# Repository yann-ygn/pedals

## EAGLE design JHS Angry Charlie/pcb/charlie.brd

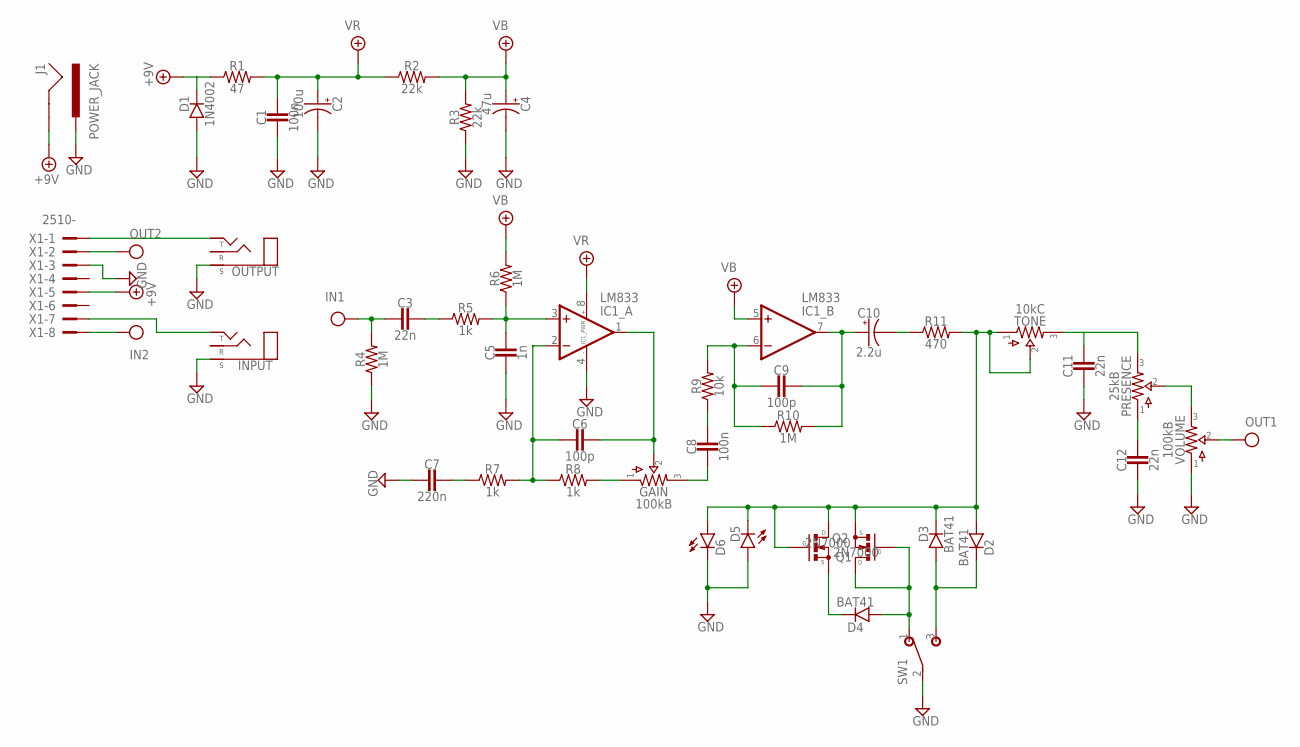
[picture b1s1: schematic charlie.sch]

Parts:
C1: 100n; 050X030_025_2
C2: 100u; 050_020
C3, C11, C12: 22n; BOX_SMALL
C4: 47u; 050_020
C5: 1n; BOX_SMALL
C6, C9: 100p; 050X030_025_2
C7: 220n; BOX_SMALL
C8: 100n; BOX_SMALL
C10: 2.2u; 050_020
D1: 1N4002; DO41-2
D2, D3, D4: BAT41; DO35-2
D5, D6: LED; 3MM_D
GAIN: 100kB; 16MM
IC1: LM833; DIL08
INPUT: STEREONMJ; NMJ6HCD2
J1: POWER_JACK; POWER_JACK_PTH
OUTPUT: STEREONMJ; NMJ6HCD2
PRESENCE: 25kB; 16MM
Q1, Q2: 2N7000; TO92-
R1: 47; R0207/3
R2, R3: 22k; R0207/3
R4, R6, R10: 1M; R0207/3
R5, R7, R8: 1k; R0207/3
R9: 10k; R0207/3
R11: 470; R0207/3
SW1: SPDT; M9040P
TONE: 10kC; 16MM
VOLUME: 100kB; 16MM
X1: 2510-; PAK100/2500-10

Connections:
+9V: D1.C, J1.GND, R1.1, X1.5
GND: C1.2, C2.-, C4.-, C5.2, C7.2, C11.2, C12.2, D1.A, D5.ANODE (A), D6.P$1 (C), IC1.4 (V-), INPUT.S, J1.PWR, OUTPUT.S, R3.1, R4.1, SW1.2, VOLUME.1, X1.3
IN: C3.2, R4.2, X1.8
unnamed: C3.1, R5.1
unnamed: INPUT.T, X1.7
unnamed: C5.1, IC1.3 (+IN), R5.2, R6.1
unnamed: OUTPUT.T, X1.1
unnamed: C6.2, IC1.2 (-IN), R7.2, R8.1
unnamed: C7.1, R7.1
unnamed: C6.1, GAIN.2, IC1.1 (OUT)
unnamed: C11.1, PRESENCE.3, TONE.3
unnamed: GAIN.1, R8.2
unnamed: C8.2, GAIN.3
unnamed: C8.1, R9.1
unnamed: C9.2, IC1.6 (-IN), R9.2, R10.1
unnamed: C9.1, C10.+, IC1.7 (OUT), R10.2
unnamed: C10.-, R11.1
unnamed: D4.A, Q1.1 (D), Q1.2 (G), SW1.1 (O)
unnamed: D4.C, Q2.3 (S)
unnamed: D2.A, D3.C, D5.P$1 (C), D6.ANODE (A), Q1.3 (S), Q2.1 (D), Q2.2 (G), R11.2, TONE.1, TONE.2
unnamed: D2.C, D3.A, SW1.3 (S)
unnamed: C12.1, PRESENCE.1
unnamed: PRESENCE.2, VOLUME.3
OUT: VOLUME.2, X1.2
VB: C4.+, IC1.5 (+IN), R2.2, R3.2, R6.2
VR: C1.1, C2.+, IC1.8 (V+), R1.2, R2.1

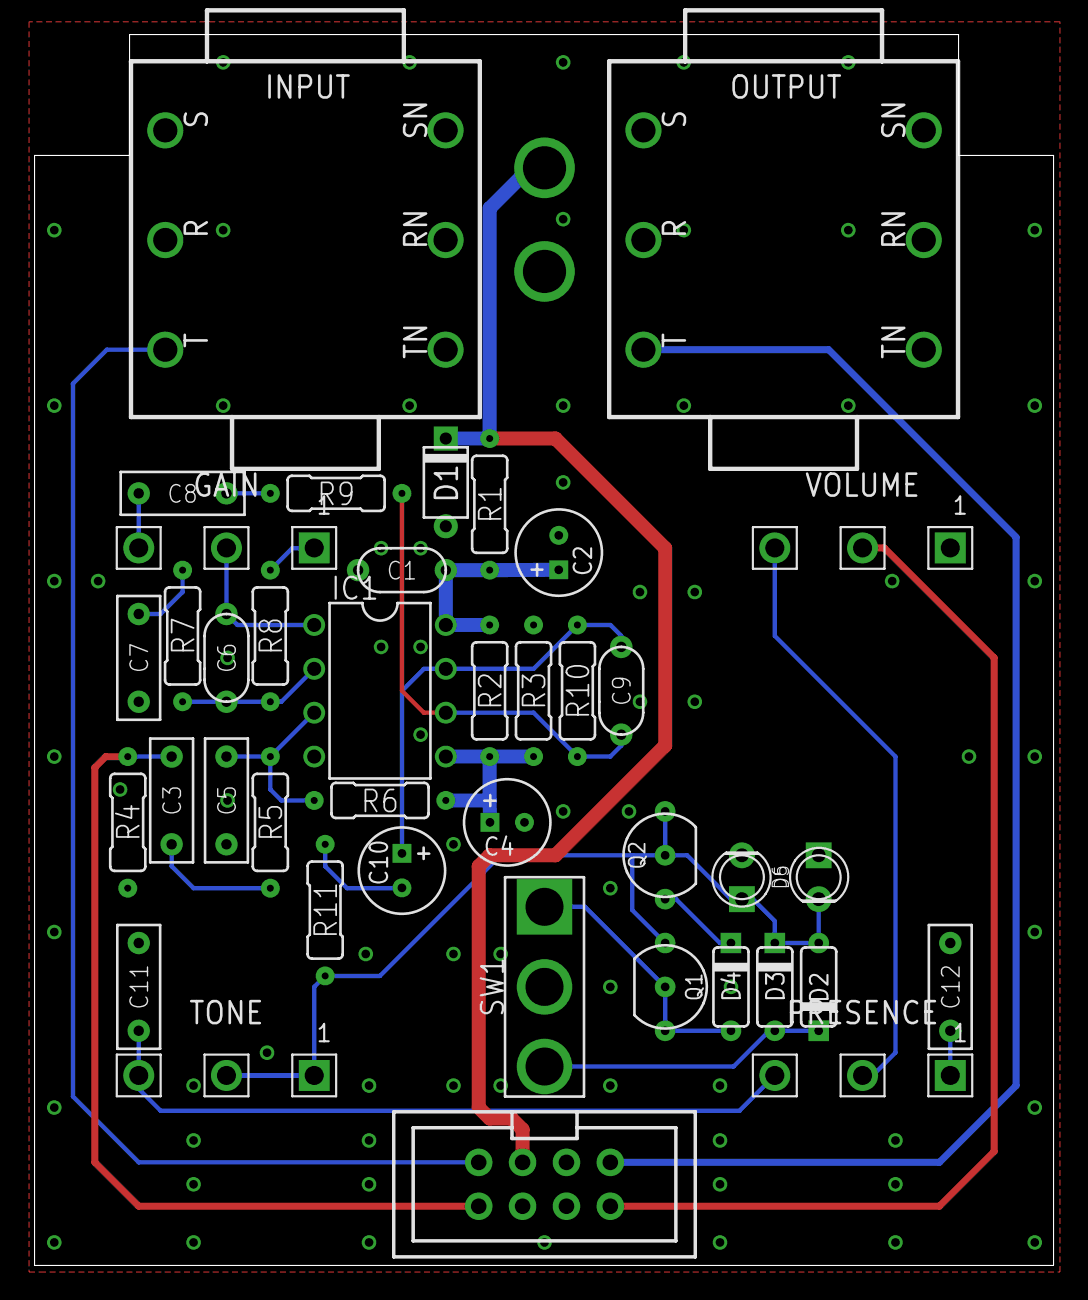
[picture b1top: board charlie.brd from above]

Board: 2 copper layers, 59.0 x 71.3 mm, 42 parts (1 on the bottom side), 26 nets.

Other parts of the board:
U$1: 125B_PCB

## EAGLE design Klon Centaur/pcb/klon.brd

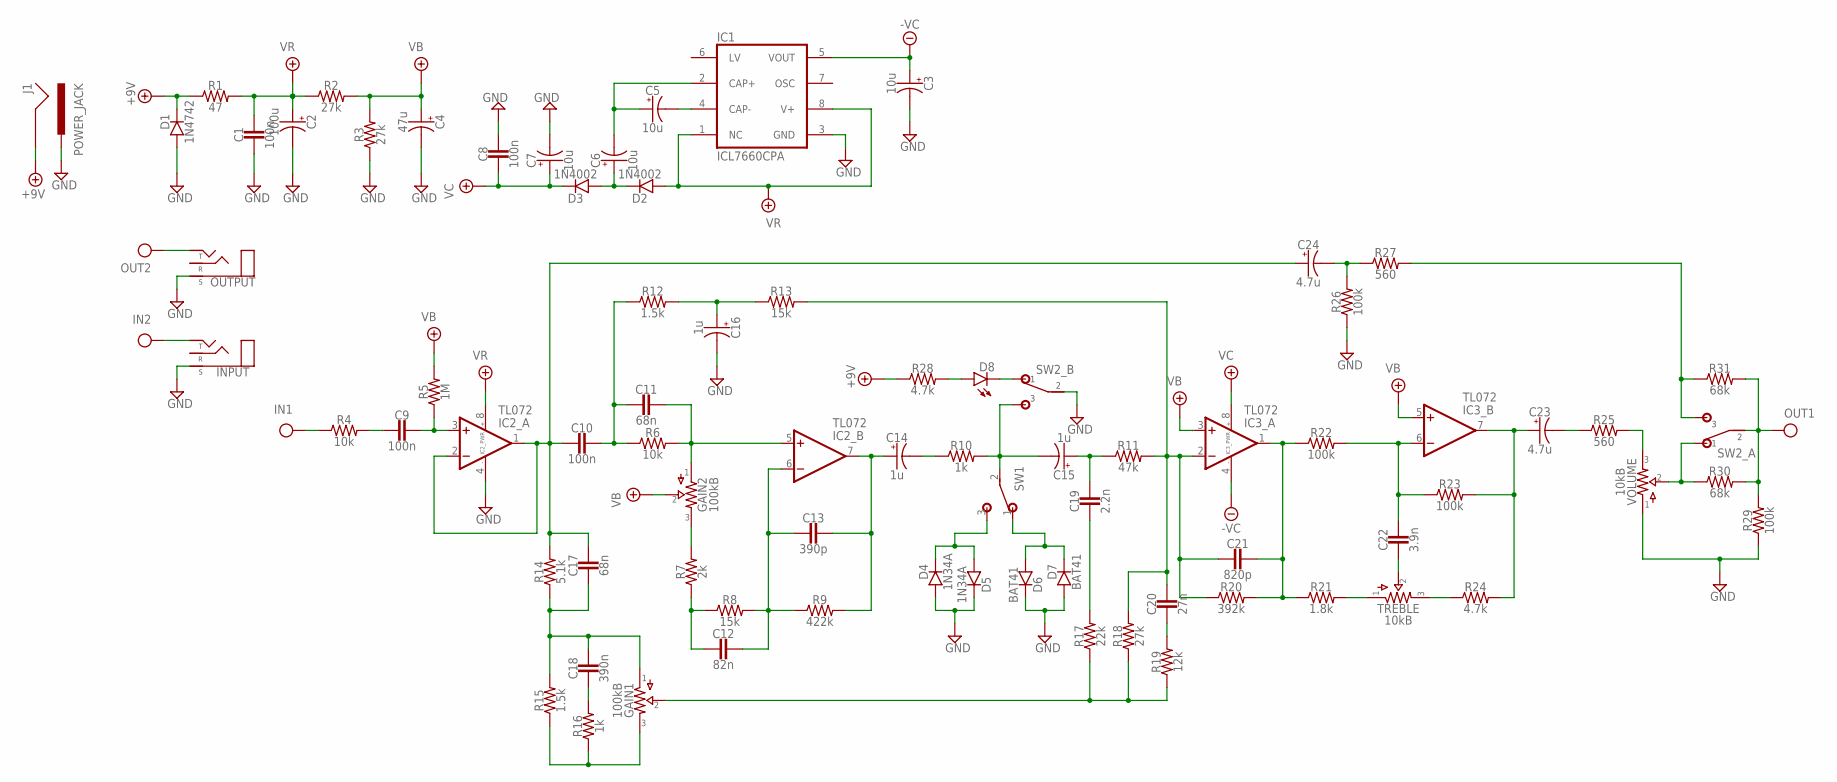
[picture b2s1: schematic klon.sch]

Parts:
C1, C8: 100n; 050X030_025_2
C2: 100u; 050_020
C3, C5, C6, C7: 10u; 050_020
C4: 47u; 050_020
C9, C10: 100n; BOX_SMALL
C11, C17: 68n; BOX_SMALL
C12: 82n; BOX_SMALL
C13: 390p; 050X030_025_2
C14, C15, C16: 1u; 040_020
C18: 390n; BOX_MED
C19: 2.2n; BOX_SMALL
C20: 27n; BOX_SMALL
C21: 820p; 050X030_025_2
C22: 3.9n; BOX_SMALL
C23, C24: 4.7u; 050_020
D1: 1N4742; DO41-2
D2, D3: 1N4002; DO41-2
D4, D5: 1N34A; DO35-2
D6, D7: BAT41; DO35-2
D8: LEDA; 3MM_A
GAIN1, GAIN2: 100kB; 16MM
IC1: ICL7660CPA; DIL08
IC2, IC3: TL072; DIL0
INPUT: STEREONMJ; NMJ6HCD2
J1: POWER_JACK; POWER_JACK_PTH
OUTPUT: STEREONMJ; NMJ6HCD2
R1: 47; R0207/3
R2, R3, R18: 27k; R0207/3
R4, R6: 10k; R0207/3
R5: 1M; R0207/3
R7: 2k; R0207/3
R8, R13: 15k; R0207/3
R9: 422k; R0207/3
R10, R16: 1k; R0207/3
R11: 47k; R0207/3
R12, R15: 1.5k; R0207/3
R14: 5.1k; R0207/3
R17: 22k; R0207/3
R19: 12k; R0207/3
R20: 392k; R0207/3
R21: 1.8k; R0207/3
R22, R23, R26, R29: 100k; R0207/3
R24, R28: 4.7k; R0207/3
R25, R27: 560; R0207/3
R30, R31: 68k; R0207/3
SW1: SPDT; M9040P
SW2: DPDTPADS; DPDT_PADS
TREBLE: 10kB; 16MM
VOLUME: 10kB; 16MM

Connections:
+9V: D1.C, J1.GND, R1.1, R28.1
-VC: C3.+, IC1.5 (VOUT), IC3.4 (V-)
GND: C1.2, C2.-, C3.-, C4.-, C7.-, C8.1, C16.-, D1.A, D4.A, D5.C, D6.C, D7.A, IC1.3 (GND), IC2.4 (V-), INPUT.S, J1.PWR, OUTPUT.S, R3.1, R26.1, R29.1, SW2.P$5 (2), VOLUME.1
IN: INPUT.T, R4.1
unnamed: C9.2, R4.2
unnamed: C5.-, IC1.4 (CAP-)
unnamed: C5.+, C6.-, IC1.2 (CAP+)
unnamed: C6.+, D2.C, D3.A
unnamed: C9.1, IC2.3 (+IN), R5.1
unnamed: C10.2, C17.1, C24.+, IC2.1 (OUT), IC2.2 (-IN), R14.2
unnamed: C10.1, C11.2, R6.1, R12.1
unnamed: C11.1, GAIN2.1, IC2.5 (+IN), R6.2
unnamed: D4.C, D5.A, SW1.3 (S)
unnamed: GAIN2.3, R7.2
unnamed: C12.2, R7.1, R8.1
unnamed: C12.1, C13.2, IC2.6 (-IN), R8.2, R9.1
unnamed: D6.A, D7.C, SW1.1 (O)
unnamed: C13.1, C14.+, IC2.7 (OUT), R9.2
unnamed: C15.+, C19.1, R11.1
unnamed: C14.-, R10.1
unnamed: C15.-, R10.2, SW1.2, SW2.P$6 (3)
unnamed: C16.+, R12.2, R13.1
unnamed: C21.1, IC3.1 (OUT), R20.2, R21.1, R22.1
unnamed: C17.2, C18.1, GAIN1.1, R14.1, R15.2
unnamed: GAIN1.3, R15.1, R16.1
unnamed: C18.2, R16.2
unnamed: GAIN1.2, R17.1, R18.1, R19.1
unnamed: C19.2, R17.2
unnamed: C20.1, C21.2, IC3.2 (-IN), R11.2, R13.2, R18.2, R20.1
unnamed: C20.2, R19.2
unnamed: R21.2, TREBLE.1
unnamed: R24.1, TREBLE.3
unnamed: C22.1, IC3.6 (-IN), R22.2, R23.1
unnamed: C22.2, TREBLE.2
unnamed: C23.+, IC3.7 (OUT), R23.2, R24.2
unnamed: C24.-, R26.2, R27.1
unnamed: R27.2, R31.1, SW2.P$3 (3)
unnamed: D8.K (C), SW2.P$4 (1)
unnamed: D8.A, R28.2
unnamed: C23.-, R25.1
unnamed: R25.2, VOLUME.3
unnamed: R30.1, SW2.P$1 (1), VOLUME.2
OUT: OUTPUT.T, R29.2, R30.2, R31.2, SW2.P$2 (2)
VB: C4.+, GAIN2.2, IC3.3 (+IN), IC3.5 (+IN), R2.2, R3.2, R5.2
VC: C7.+, C8.2, D3.C, IC3.8 (V+)
VR: C1.1, C2.+, D2.A, IC1.1 (NC), IC1.8 (V+), IC2.8 (V+), R1.2, R2.1

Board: 2 copper layers, 76 parts (1 on the bottom side), 46 nets, no tracks yet.

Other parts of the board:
U$1: 125B_PCB

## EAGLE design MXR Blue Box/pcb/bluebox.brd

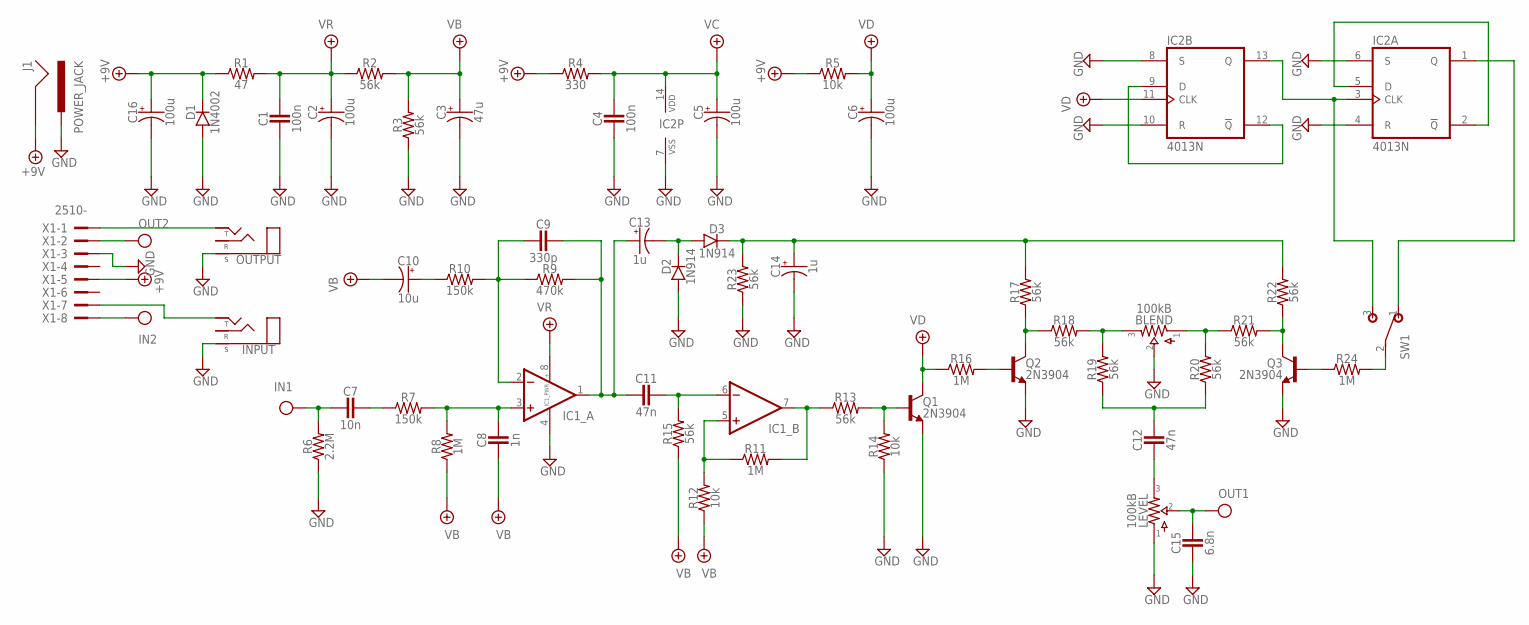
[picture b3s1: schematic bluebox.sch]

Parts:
BLEND: 100kB; 16MM
C1, C4: 100n; 050X030_025_2
C2, C5, C6, C16: 100u; 050_020
C3: 47u; 050_020
C7: 10n; BOX_SMALL
C8: 1n; BOX_SMALL
C9: 330p; 050X030_025_2
C10: 10u; 050_020
C11, C12: 47n; BOX_SMALL
C13, C14: 1u; 040_020
C15: 6.8n; BOX_SMALL
D1: 1N4002; DO41-2
D2, D3: 1N914; DO35-2
IC1: DUALTH; DIL0
IC2: 4013N; DIL14
INPUT: STEREONMJ; NMJ6HCD2
J1: POWER_JACK; POWER_JACK_PTH
LEVEL: 100kB; 16MM
OUTPUT: STEREONMJ; NMJ6HCD2
Q1, Q2, Q3: 2N3904; TO92-
R1: 47; R0207/3
R2, R3, R13, R15, R17, R18, R19, R20, R21, R22, R23: 56k; R0207/3
R4: 330; R0207/3
R5, R12, R14: 10k; R0207/3
R6: 2.2M; R0207/3
R7, R10: 150k; R0207/3
R8, R11, R16, R24: 1M; R0207/3
R9: 470k; R0207/3
SW1: SPDTPIN_MOUNT; 1MS1T1B1C0M2QE
X1: 2510-; PAK100/2500-10

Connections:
+9V: C16.+, D1.C, J1.GND, R1.1, R4.1, R5.1, X1.5
GND: BLEND.2, C1.2, C2.-, C3.-, C4.2, C5.-, C6.-, C14.-, C15.2, C16.-, D1.A, D2.A, IC1.4 (V-), IC2.4 (R), IC2.6 (S), IC2.7 (VSS), IC2.8 (S), IC2.10 (R), INPUT.S, J1.PWR, LEVEL.1, OUTPUT.S, Q1.3 (E), Q2.3 (E), Q3.3 (E), R3.1, R6.1, R14.1, R23.1, X1.3
IN: C7.2, R6.2, X1.8
unnamed: Q3.1 (C), R21.2, R22.1
unnamed: INPUT.T, X1.7
unnamed: C7.1, R7.1
unnamed: OUTPUT.T, X1.1
unnamed: C8.1, IC1.3 (+IN), R7.2, R8.2
unnamed: C9.2, IC1.2 (-IN), R9.1, R10.2
unnamed: C9.1, C11.2, C13.+, IC1.1 (OUT), R9.2
unnamed: C10.+, R10.1
unnamed: C11.1, IC1.6 (-IN), R15.2
unnamed: IC1.5 (+IN), R11.1, R12.2
unnamed: IC1.7 (OUT), R11.2, R13.1
unnamed: Q1.2 (B), R13.2, R14.2
unnamed: Q2.2 (B), R16.2
unnamed: Q2.1 (C), R17.1, R18.1
unnamed: BLEND.3, R18.2, R19.2
unnamed: BLEND.1, R20.2, R21.1
unnamed: C12.1, R19.1, R20.1
unnamed: C14.+, D3.C, R17.2, R22.2, R23.2
unnamed: Q3.2 (B), R24.1
unnamed: C13.-, D2.C, D3.A
unnamed: C12.2, LEVEL.3
unnamed: IC2.3 (CLK), IC2.13 (Q), SW1.3 (S)
unnamed: IC2.9 (D), IC2.12 (!Q)
unnamed: IC2.1 (Q), SW1.1 (O)
unnamed: IC2.2 (!Q), IC2.5 (D)
unnamed: R24.2, SW1.2
OUT: C15.1, LEVEL.2, X1.2
VB: C3.+, C8.2, C10.-, R2.2, R3.2, R8.1, R12.1, R15.1
VC: C4.1, C5.+, IC2.14 (VDD), R4.2
VD: C6.+, IC2.11 (CLK), Q1.1 (C), R5.2, R16.1
VR: C1.1, C2.+, IC1.8 (V+), R1.2, R2.1

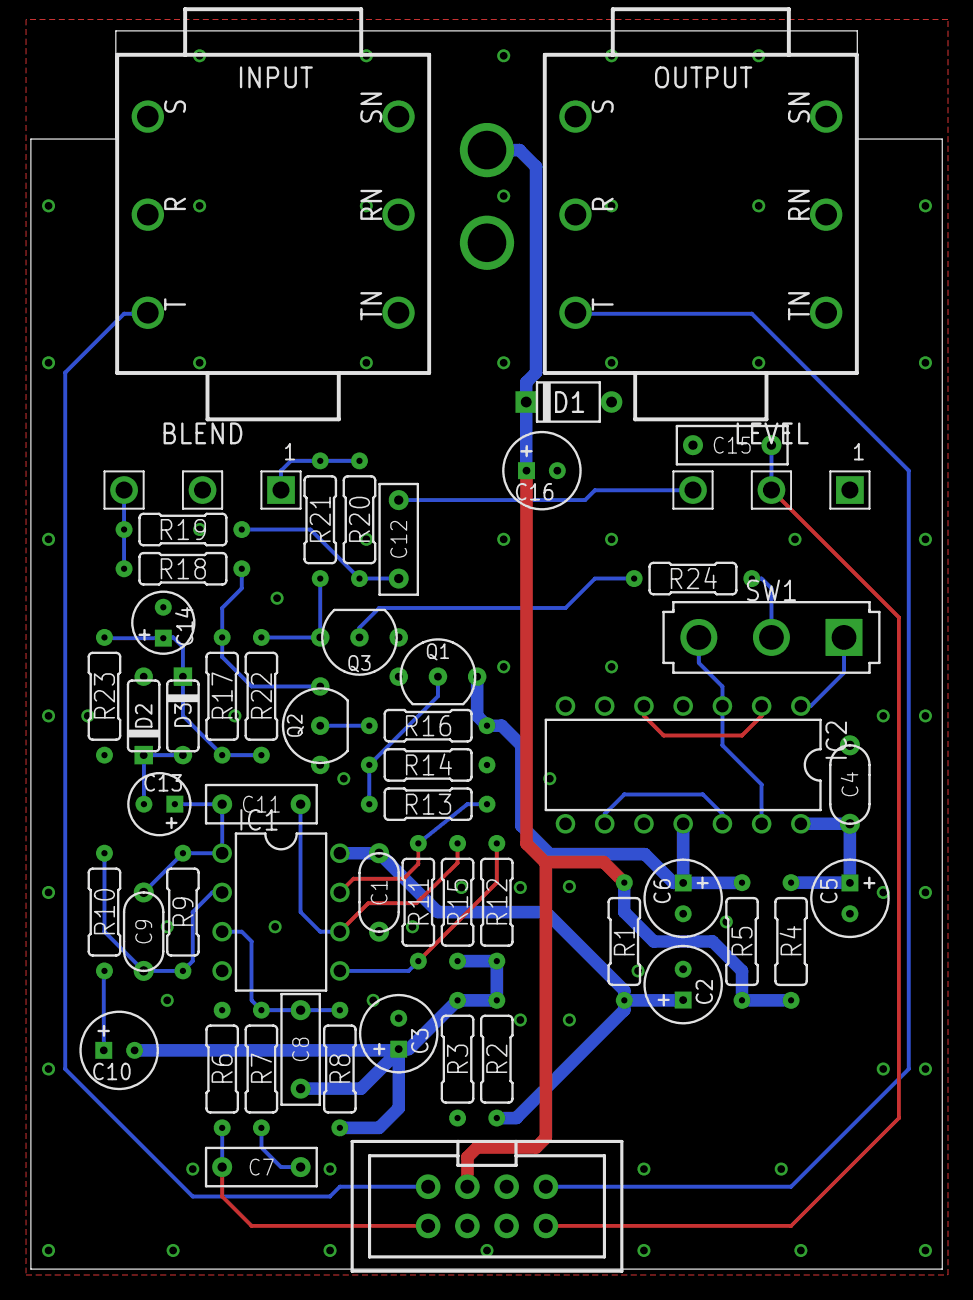
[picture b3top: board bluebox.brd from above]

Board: 2 copper layers, 59.0 x 80.2 mm, 56 parts (1 on the bottom side), 34 nets.

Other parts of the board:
U$2: 125B_PCB_HUGE

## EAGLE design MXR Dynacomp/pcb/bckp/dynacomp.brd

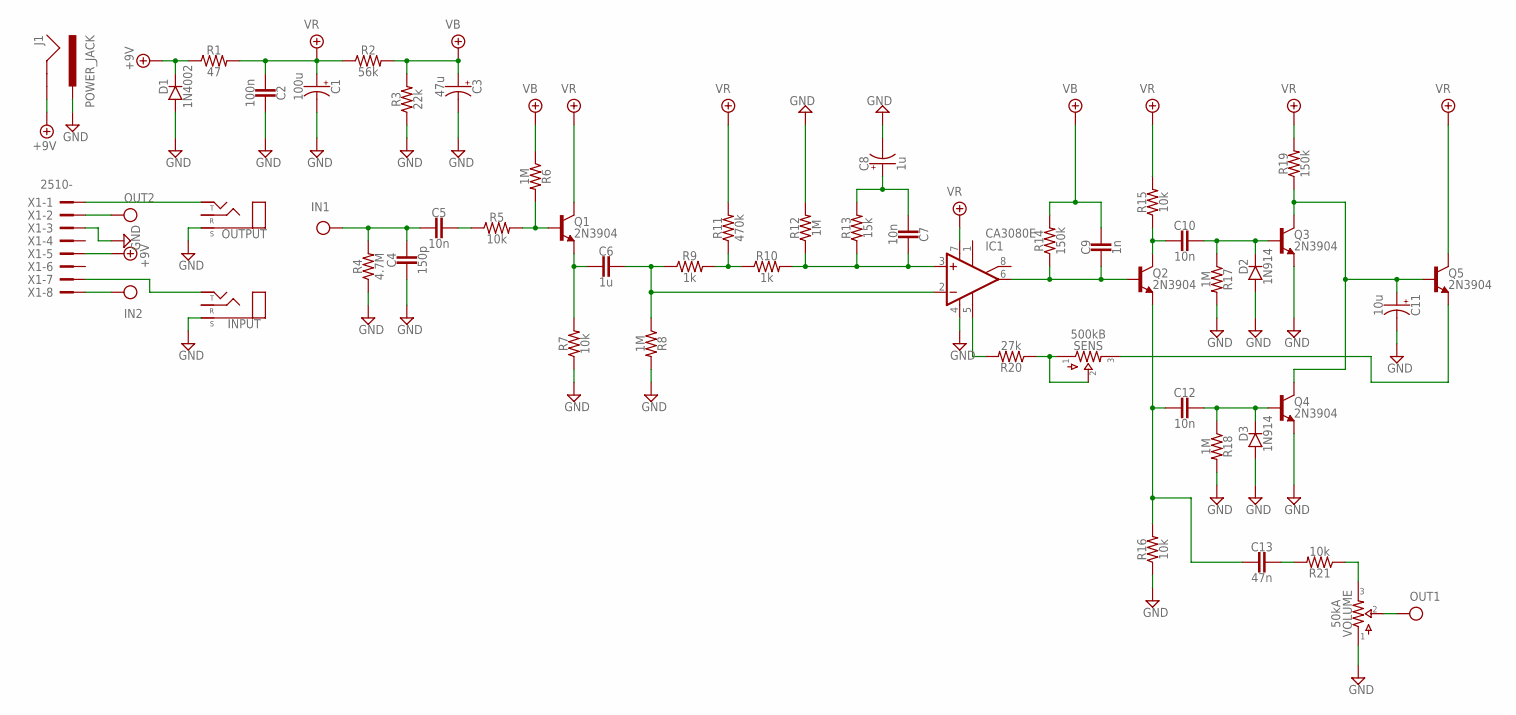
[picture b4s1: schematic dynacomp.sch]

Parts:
C1: 100u; 040_020
C2: 100n; 050X030_025_2
C3: 47u; 040_020
C4: 150p; 050X030_025_2
C5, C7, C10, C12: 10n; BOX_SMALL
C6: 1u; BOX_BIG
C8: 1u; 040_020
C9: 1n; BOX_SMALL
C11: 10u; 040_020
C13: 47n; BOX_SMALL
D1: 1N4002; DO41-2
D2, D3: 1N914; DO35-2
IC1: CA3080E; DIL08
INPUT: STEREONMJ; NMJ6HCD2
J1: POWER_JACK; POWER_JACK_PTH
OUTPUT: STEREONMJ; NMJ6HCD2
Q1, Q2, Q3, Q4, Q5: 2N3904; TO92-
R1: 47; R0207/3
R2: 56k; R0207/3
R3: 22k; R0207/3
R4: 4.7M; R0207/3
R5, R7, R15, R16, R21: 10k; R0207/3
R6, R8, R12, R17, R18: 1M; R0207/3
R9, R10: 1k; R0207/3
R11: 470k; R0207/3
R13: 15k; R0207/3
R14, R19: 150k; R0207/3
R20: 27k; R0207/3
SENS: 500kB; 16MM
VOLUME: 50kA; 16MM
X1: 2510-; PAK100/2500-10

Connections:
+9V: D1.C, J1.GND, R1.1, X1.5
C8: C6.1, IC1.2 (-IN), R8.1, R9.1
C10: C7.2, C8.+, R13.2
C40: C13.1, R21.2
GND: C1.-, C2.1, C3.-, C4.2, C8.-, C11.-, D1.A, D2.A, D3.A, IC1.4 (V-), INPUT.S, J1.PWR, OUTPUT.S, Q3.3 (E), Q4.3 (E), R3.1, R4.1, R7.1, R8.2, R12.2, R16.1, R17.2, R18.2, VOLUME.1, X1.3
IN: C4.1, C5.2, R4.2, X1.8
unnamed: C12.2, C13.2, Q2.3 (E), R16.2
unnamed: INPUT.T, X1.7
unnamed: C5.1, R5.1
unnamed: OUTPUT.T, X1.1
unnamed: Q1.2 (B), R5.2, R6.2
unnamed: IC1.5 (OPT), R20.2
unnamed: C11.+, Q3.1 (C), Q4.1 (C), Q5.2 (B), R19.1
unnamed: C6.2, Q1.3 (E), R7.2
unnamed: C7.1, IC1.3 (+IN), R10.2, R12.1, R13.1
unnamed: R9.2, R10.1, R11.1
unnamed: R20.1, SENS.1, SENS.2
unnamed: Q5.3 (E), SENS.3
unnamed: C10.2, Q2.1 (C), R15.1
unnamed: C9.2, IC1.6 (OUT), Q2.2 (B), R14.1
unnamed: R21.1, VOLUME.3
unnamed: C10.1, D2.C, Q3.2 (B), R17.1
unnamed: C12.1, D3.C, Q4.2 (B), R18.1
OUT: VOLUME.2, X1.2
VB: C3.+, C9.1, R2.2, R3.2, R6.1, R14.2
VR: C1.+, C2.2, IC1.7 (V+), Q1.1 (C), Q5.1 (C), R1.2, R2.1, R11.2, R15.2, R19.2

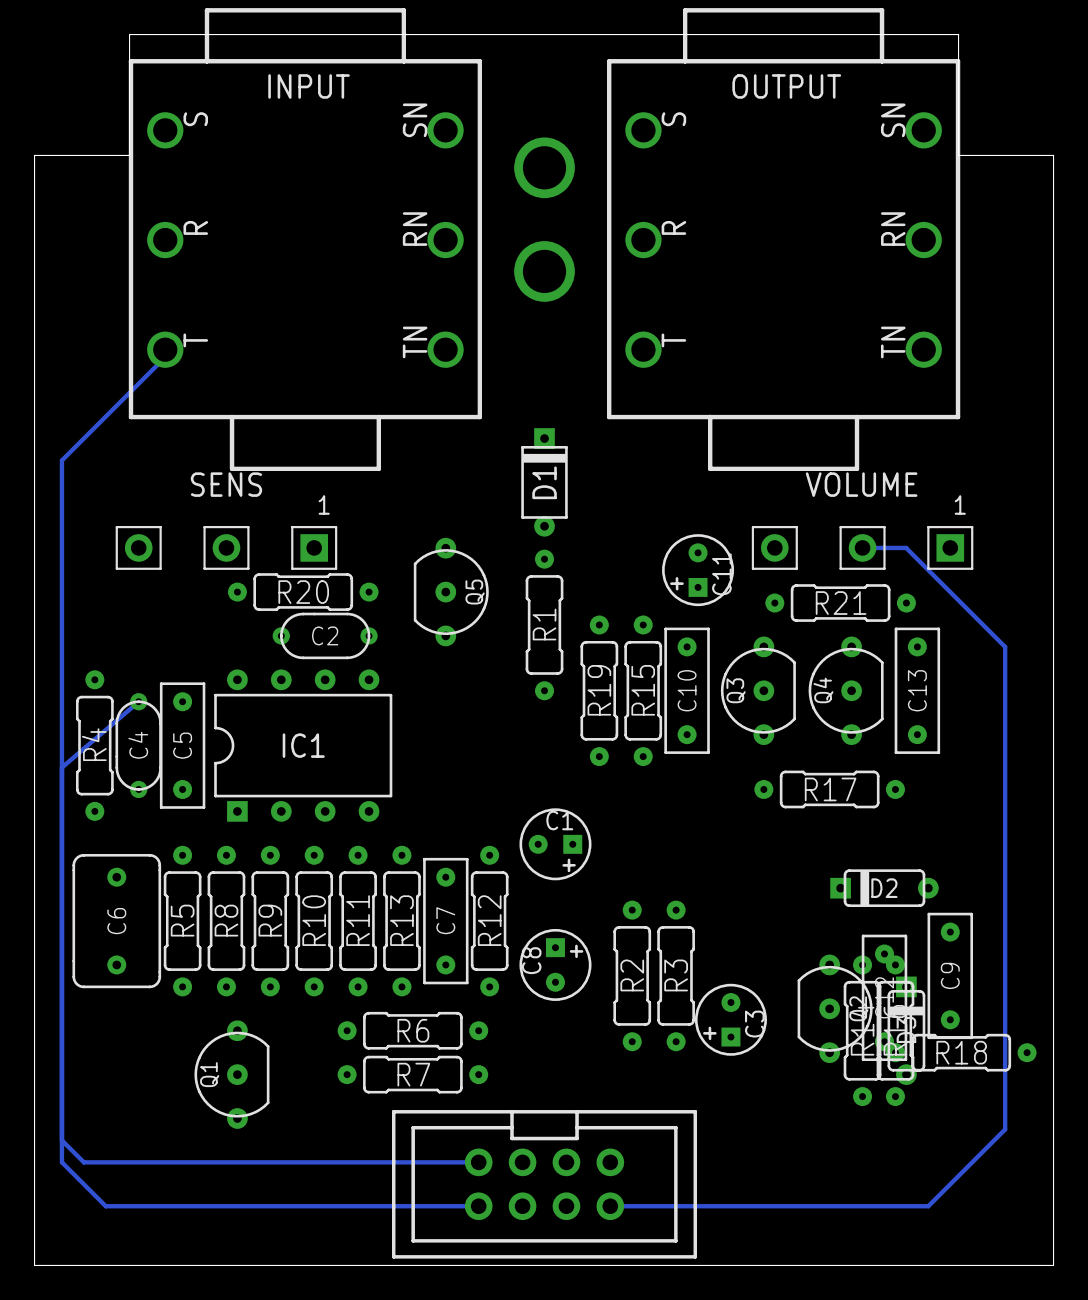
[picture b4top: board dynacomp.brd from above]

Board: 2 copper layers, 59.0 x 71.3 mm, 50 parts (1 on the bottom side), 26 nets.

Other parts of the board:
U$1: 125B_PCB

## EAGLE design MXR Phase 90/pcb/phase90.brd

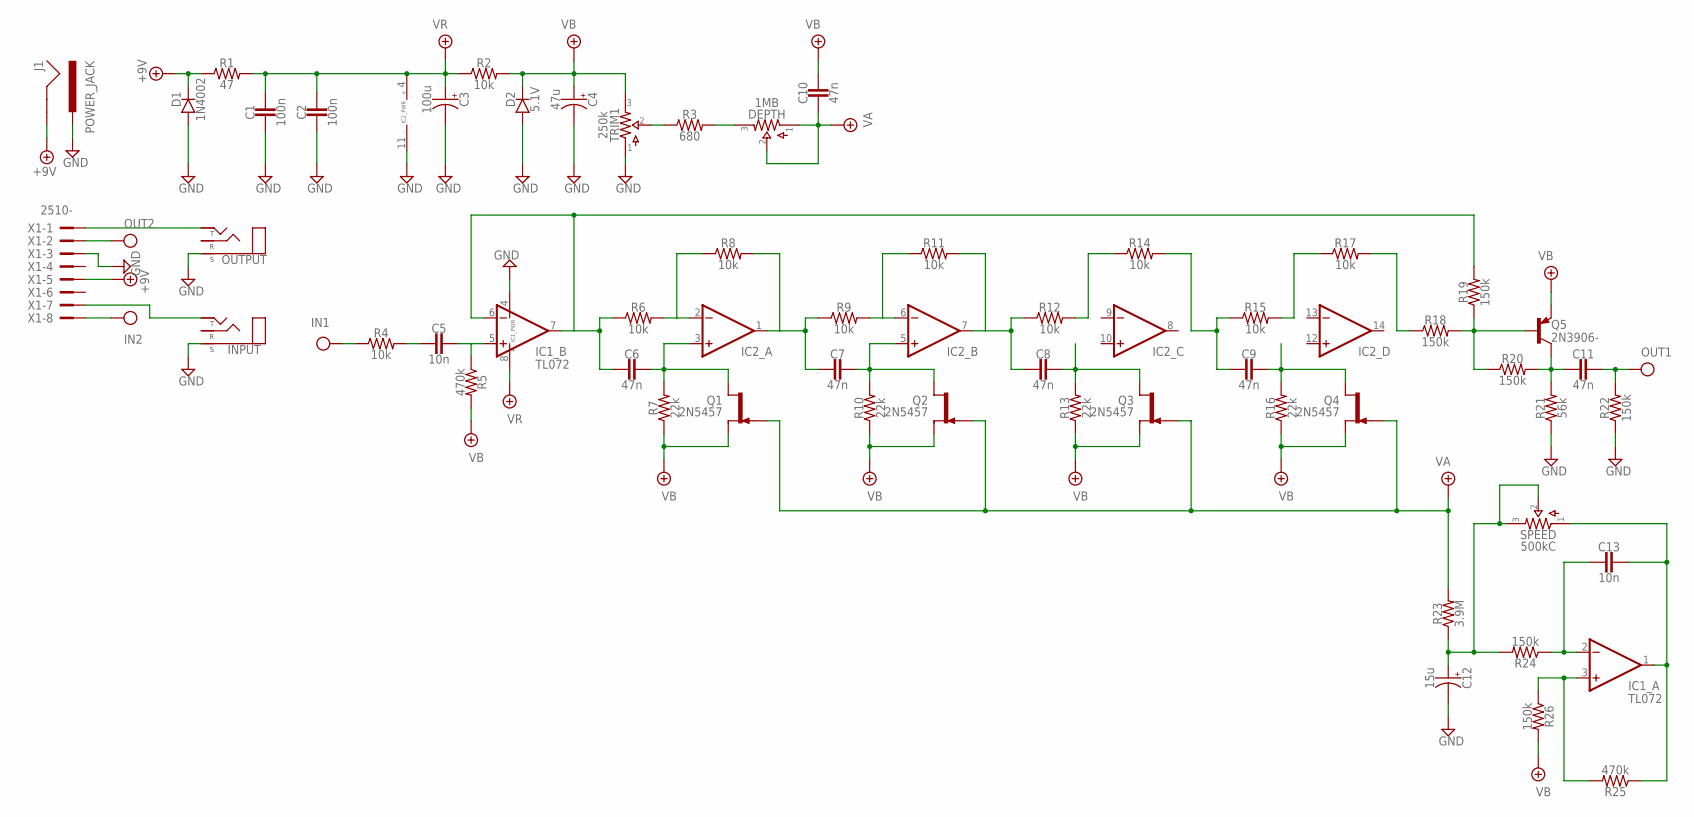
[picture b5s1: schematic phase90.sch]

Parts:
C1, C2: 100n; 050X030_025_2
C3: 100u; 050_020
C4: 47u; 050_020
C5, C13: 10n; BOX_SMALL
C6, C7, C8, C9, C10, C11: 47n; BOX_SMALL
C12: 15u; 050_020_1
D1: 1N4002; DO41-2
D2: 5.1V; DO41-2
DEPTH: 1MB; 16MM
IC1: TL072; DIL0
IC2: QUADTH; DIL14
INPUT: STEREONMJ; NMJ6HCD2
J1: POWER_JACK; POWER_JACK_PTH
OUTPUT: STEREONMJ; NMJ6HCD2
Q1, Q2, Q3, Q4: 2N5457; TO92-
Q5: 2N3906-; TO92-
R1: 47; R0207/3
R2, R4, R6, R8, R9, R11, R12, R14, R15, R17: 10k; R0207/3
R3: 680; R0207/3
R5, R25: 470k; R0207/3
R7, R10, R13, R16: 22k; R0207/3
R18, R19, R20, R22, R24, R26: 150k; R0207/3
R21: 56k; R0207/3
R23: 3.9M; R0207/3
SPEED: 500kC; 16MM
TRIM1: 250k; RTRIM3296W
X1: 2510-; PAK100/2500-10

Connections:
+9V: D1.C, J1.GND, R1.1, X1.5
GND: C1.2, C2.2, C3.-, C4.-, C12.-, D1.A, D2.A, IC1.4 (V-), IC2.11 (V-), INPUT.S, J1.PWR, OUTPUT.S, R21.1, R22.1, TRIM1.1, X1.3
IN: R4.1, X1.8
unnamed: R3.1, TRIM1.2
unnamed: INPUT.T, X1.7
unnamed: DEPTH.3, R3.2
unnamed: OUTPUT.T, X1.1
unnamed: C5.2, R4.2
unnamed: C6.2, IC1.6 (-IN), IC1.7 (OUT), R6.1, R19.2
unnamed: IC2.2 (-IN), R6.2, R8.1
unnamed: C5.1, IC1.5 (+IN), R5.1
unnamed: C6.1, IC2.3 (+IN), Q1.3 (D), R7.2
unnamed: C7.2, IC2.1 (OUT), R8.2, R9.1
unnamed 14: IC2.6 (-IN), R9.2, R11.1; also elsewhere on the board
unnamed: C7.1, IC2.5 (+IN), Q2.3 (D), R10.2
unnamed: C8.2, IC2.7 (OUT), R11.2, R12.1
unnamed: IC1.3 (+IN), R25.2, R26.1
unnamed: IC2.9 (-IN), R12.2, R14.1
unnamed: C8.1, IC2.10 (+IN), Q3.3 (D), R13.2
unnamed: C9.2, IC2.8 (OUT), R14.2, R15.1
unnamed: C13.1, IC1.1 (OUT), R25.1, SPEED.1
unnamed: IC2.13 (-IN), R15.2, R17.1
unnamed: C9.1, IC2.12 (+IN), Q4.3 (D), R16.2
unnamed 24: IC2.14 (OUT), R17.2, R18.1; also elsewhere on the board
unnamed: Q5.2 (B), R18.2, R19.1, R20.1
unnamed: C11.2, Q5.1 (C), R20.2, R21.2
unnamed: C13.2, IC1.2 (-IN), R24.1
unnamed: C12.+, R23.1, R24.2, SPEED.2, SPEED.3
OUT: C11.1, R22.2, X1.2
VA: C10.2, DEPTH.1, DEPTH.2, Q1.1 (G), Q2.1 (G), Q3.1 (G), Q4.1 (G), R23.2
VB: C4.+, C10.1, D2.C, Q1.2 (S), Q2.2 (S), Q3.2 (S), Q4.2 (S), Q5.3 (E), R2.2, R5.2, R7.1, R10.1, R13.1, R16.1, R26.2, TRIM1.3
VR: C1.1, C2.1, C3.+, IC1.8 (V+), IC2.4 (V+), R1.2, R2.1

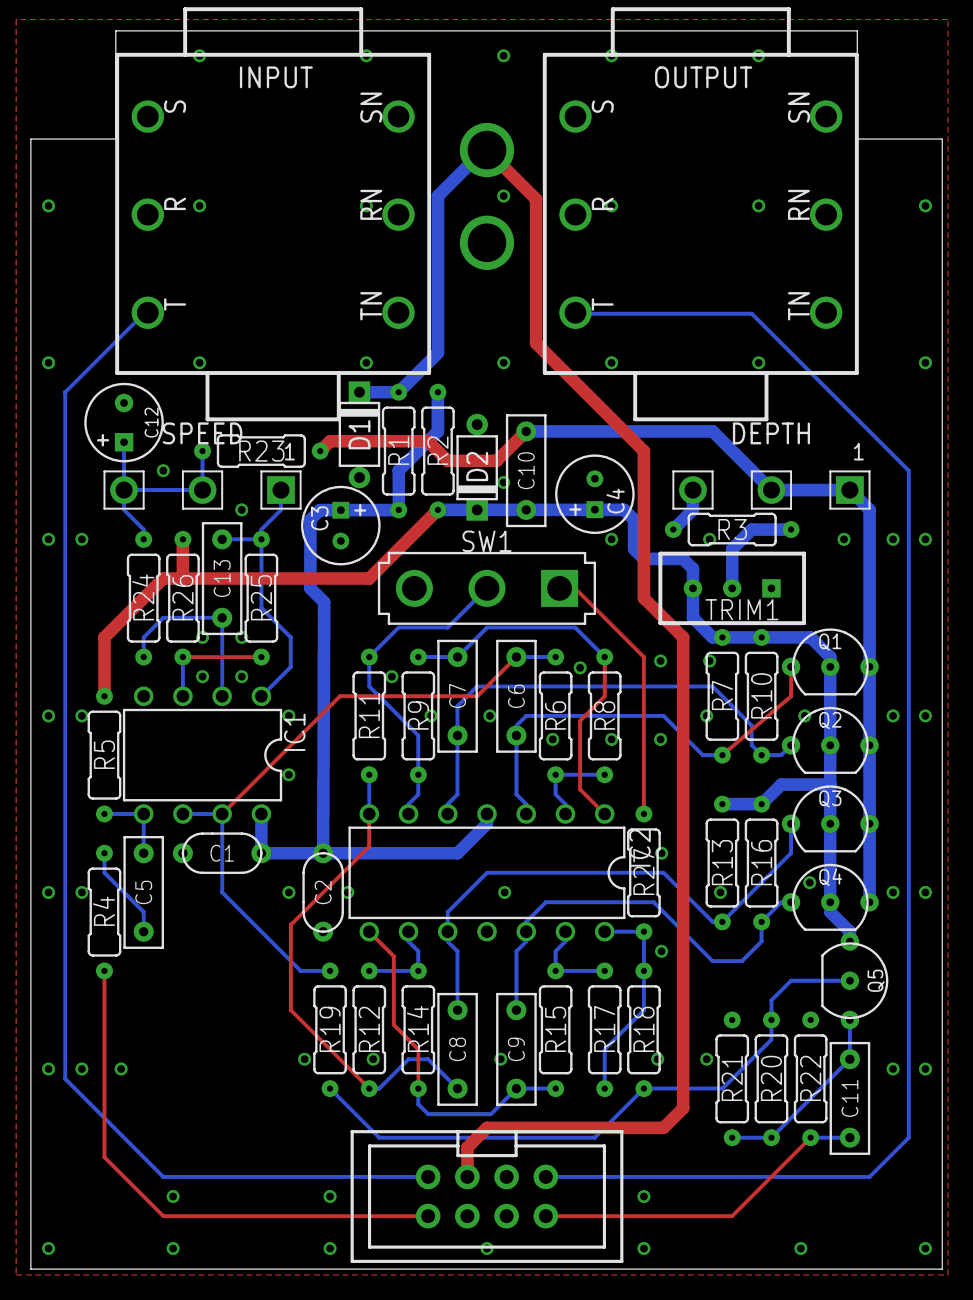
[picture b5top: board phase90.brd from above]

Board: 2 copper layers, 59.0 x 80.2 mm, 58 parts (1 on the bottom side), 33 nets.

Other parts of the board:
R27: 22k; R0207/3
SW1: 1MS1T1B1C0M2QE
U$2: 125B_PCB_HUGE

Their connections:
unnamed: R27.1, SW1.1
unnamed 14: SW1.2; also elsewhere on the board
unnamed 24: R27.2; also elsewhere on the board

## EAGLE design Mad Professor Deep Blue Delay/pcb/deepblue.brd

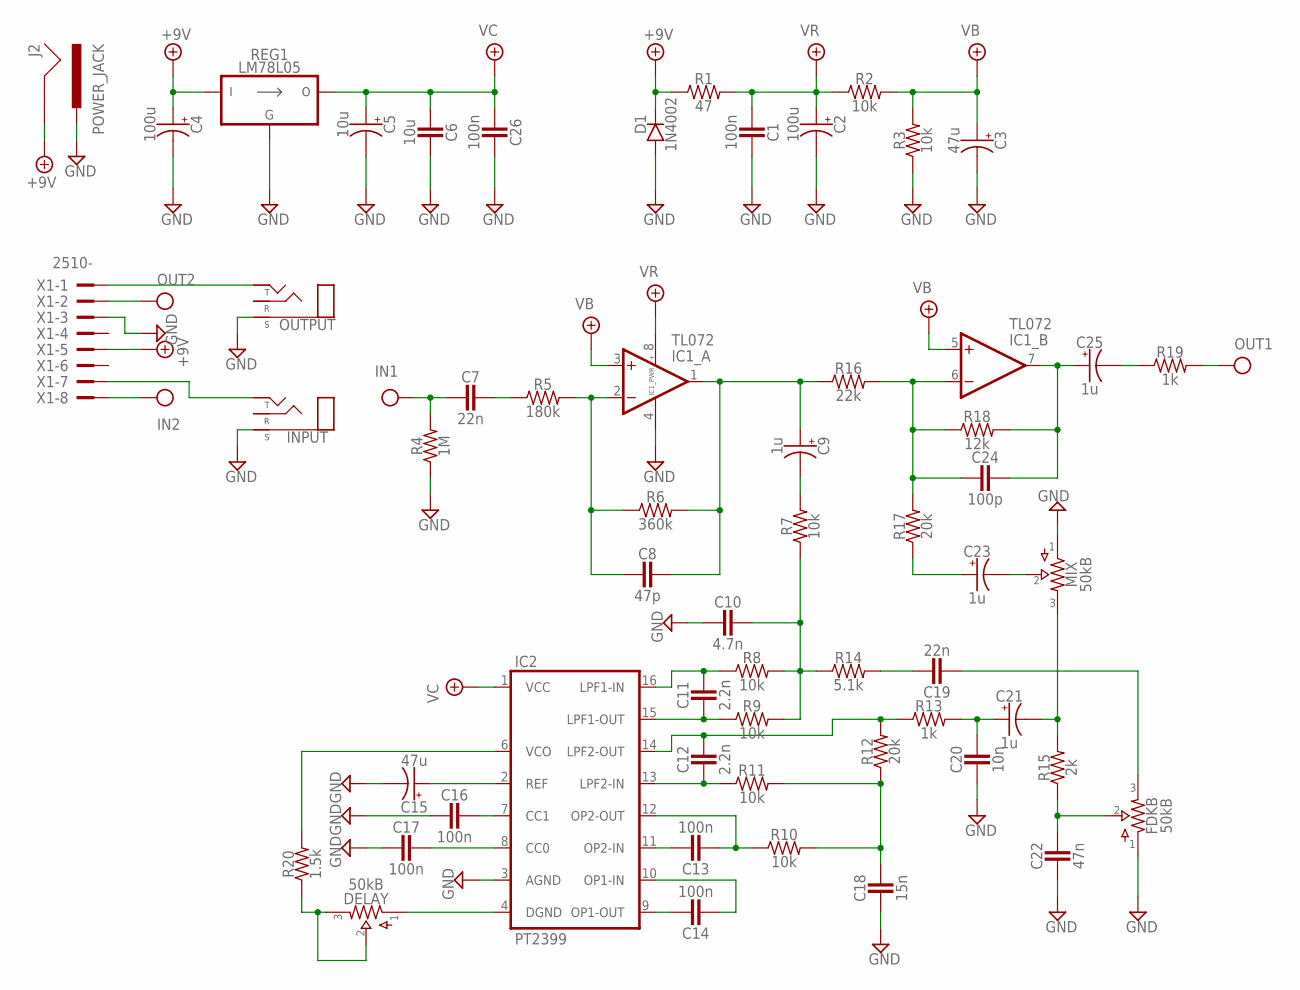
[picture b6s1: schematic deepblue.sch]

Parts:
C1, C26: 100n; 050X030_025_2
C2, C4: 100u; 050_020
C3, C15: 47u; 050_020
C5: 10u; 050_020
C6: 10u; 050X030_025
C7, C19: 22n; BOX_SMALL
C8: 47p; 050X030_025_2
C9, C21, C23, C25: 1u; 040_020
C10: 4.7n; BOX_SMALL
C11, C12: 2.2n; BOX_SMALL
C13, C14, C16, C17: 100n; BOX_SMALL
C18: 15n; BOX_SMALL
C20: 10n; BOX_SMALL
C22: 47n; BOX_SMALL
C24: 100p; 050X030_025_2
D1: 1N4002; DO41-2
DELAY: 50kB; 16MM
FDKB: 50kB; 16MM
IC1: TL072; DIL0
IC2: PT2399; DIL16
INPUT: STEREONMJ; NMJ6HCD2
J2: POWER_JACK; POWER_JACK_PTH
MIX: 50kB; 16MM
OUTPUT: STEREONMJ; NMJ6HCD2
R1: 47; R0207/3
R2, R3, R7, R8, R9, R10, R11: 10k; R0207/3
R4: 1M; R0207/3
R5: 180k; R0207/3
R6: 360k; R0207/3
R12, R17: 20k; R0207/3
R13, R19: 1k; R0207/3
R14: 5.1k; R0207/3
R15: 2k; R0207/3
R16: 22k; R0207/3
R18: 12k; R0207/3
R20: 1.5k; R0207/3
REG1: LM78L05; TO92-
X1: 2510-; PAK100/2500-10

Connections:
+18V: C4.+, D1.C, J2.GND, R1.1, REG1.1 (VI), X1.5
GND: C1.1, C2.-, C3.-, C4.-, C5.-, C6.1, C10.2, C15.-, C16.2, C17.2, C18.2, C20.2, C22.2, C26.1, D1.A, FDKB.1, IC1.4 (V-), IC2.3 (AGND), INPUT.S, J2.PWR, MIX.1, OUTPUT.S, R3.1, R4.1, REG1.2 (GND), X1.3
IN: C7.2, R4.2, X1.8
unnamed: C7.1, R5.1
unnamed: C8.2, IC1.2 (-IN), R5.2, R6.1
unnamed: C8.1, C9.+, IC1.1 (OUT), R6.2, R16.1
unnamed: C15.+, IC2.2 (REF)
unnamed: C16.1, IC2.7 (CC1)
unnamed: C17.1, IC2.8 (CC0)
unnamed: C11.2, IC2.15 (LPF1-OUT), R9.1
unnamed: C11.1, IC2.16 (LPF1-IN), R8.1
unnamed: C13.2, IC2.12 (OP2-OUT), R10.1
unnamed: C13.1, IC2.11 (OP2-IN)
unnamed: C14.2, IC2.10 (OP1-IN)
unnamed: C14.1, IC2.9 (OP1-OUT)
unnamed: C9.-, R7.2
unnamed: C10.1, R7.1, R8.2, R9.2, R14.1
unnamed: C12.2, IC2.13 (LPF2-IN), R11.1
unnamed: C12.1, IC2.14 (LPF2-OUT), R12.2, R13.1
unnamed: C18.1, R10.2, R11.2, R12.1
unnamed: C19.1, R14.2
unnamed: C20.1, C21.+, R13.2
unnamed: C21.-, MIX.3, R15.2
unnamed: C22.1, FDKB.2, R15.1
unnamed: C19.2, FDKB.3
unnamed: C23.+, R17.1
unnamed: C23.-, MIX.2
unnamed: C24.2, IC1.6 (-IN), R16.2, R17.2, R18.1
unnamed: C24.1, C25.+, IC1.7 (OUT), R18.2
unnamed: C25.-, R19.1
unnamed: DELAY.1, IC2.4 (DGND)
unnamed: DELAY.2, DELAY.3, R20.1
unnamed: IC2.6 (VCO), R20.2
unnamed: OUTPUT.T, X1.1
unnamed: INPUT.T, X1.7
OUT: R19.2, X1.2
VB: C3.+, IC1.3 (+IN), IC1.5 (+IN), R2.2, R3.2
VC: C5.+, C6.2, C26.2, IC2.1 (VCC), REG1.3 (VO)
VR: C1.2, C2.+, IC1.8 (V+), R1.2, R2.1

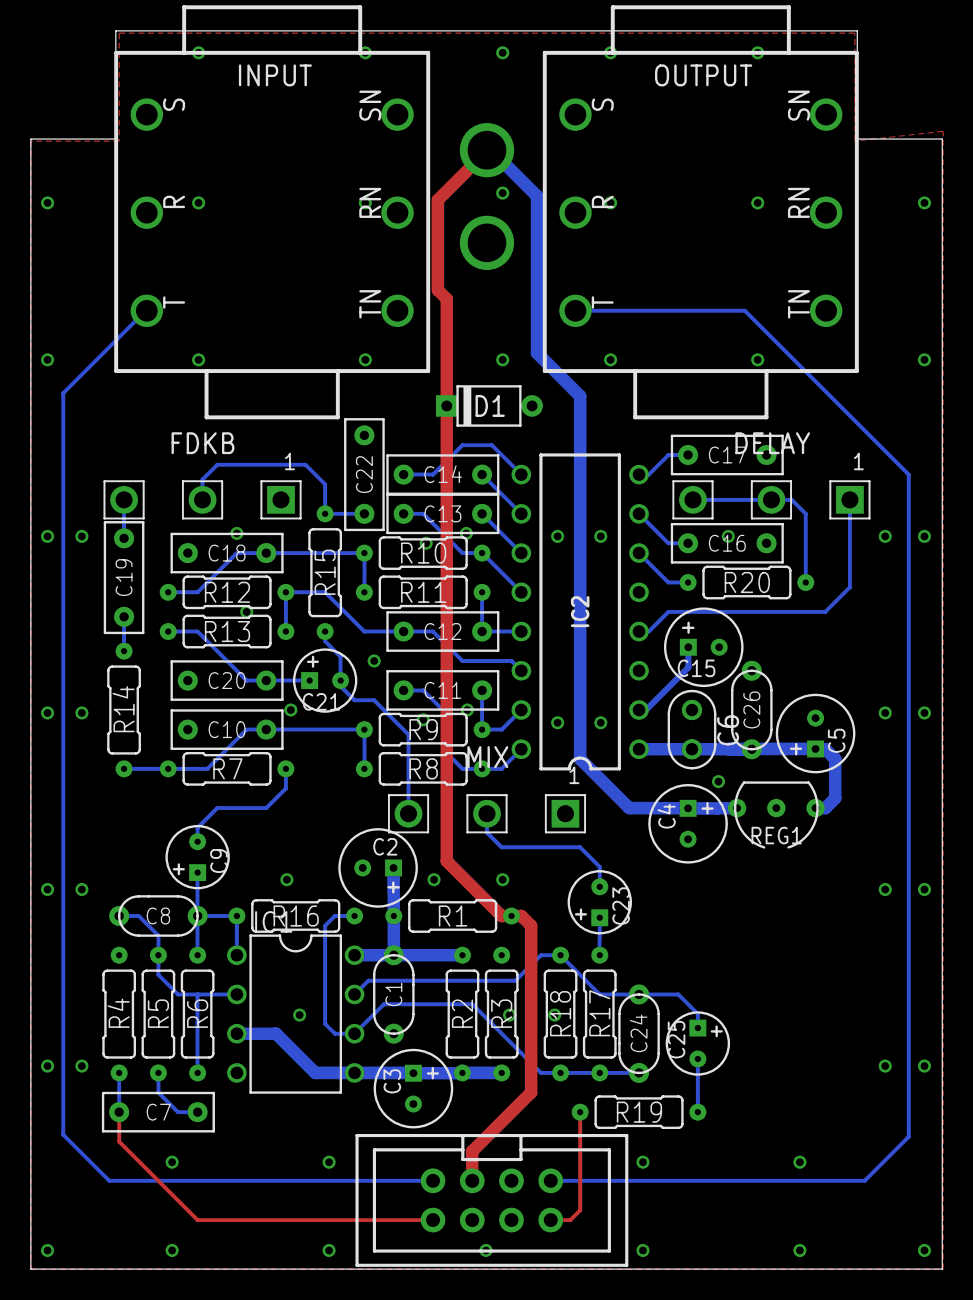
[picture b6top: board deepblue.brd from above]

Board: 2 copper layers, 59.0 x 80.2 mm, 58 parts (1 on the bottom side), 39 nets.

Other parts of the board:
U$2: 125B_PCB_HUGE
